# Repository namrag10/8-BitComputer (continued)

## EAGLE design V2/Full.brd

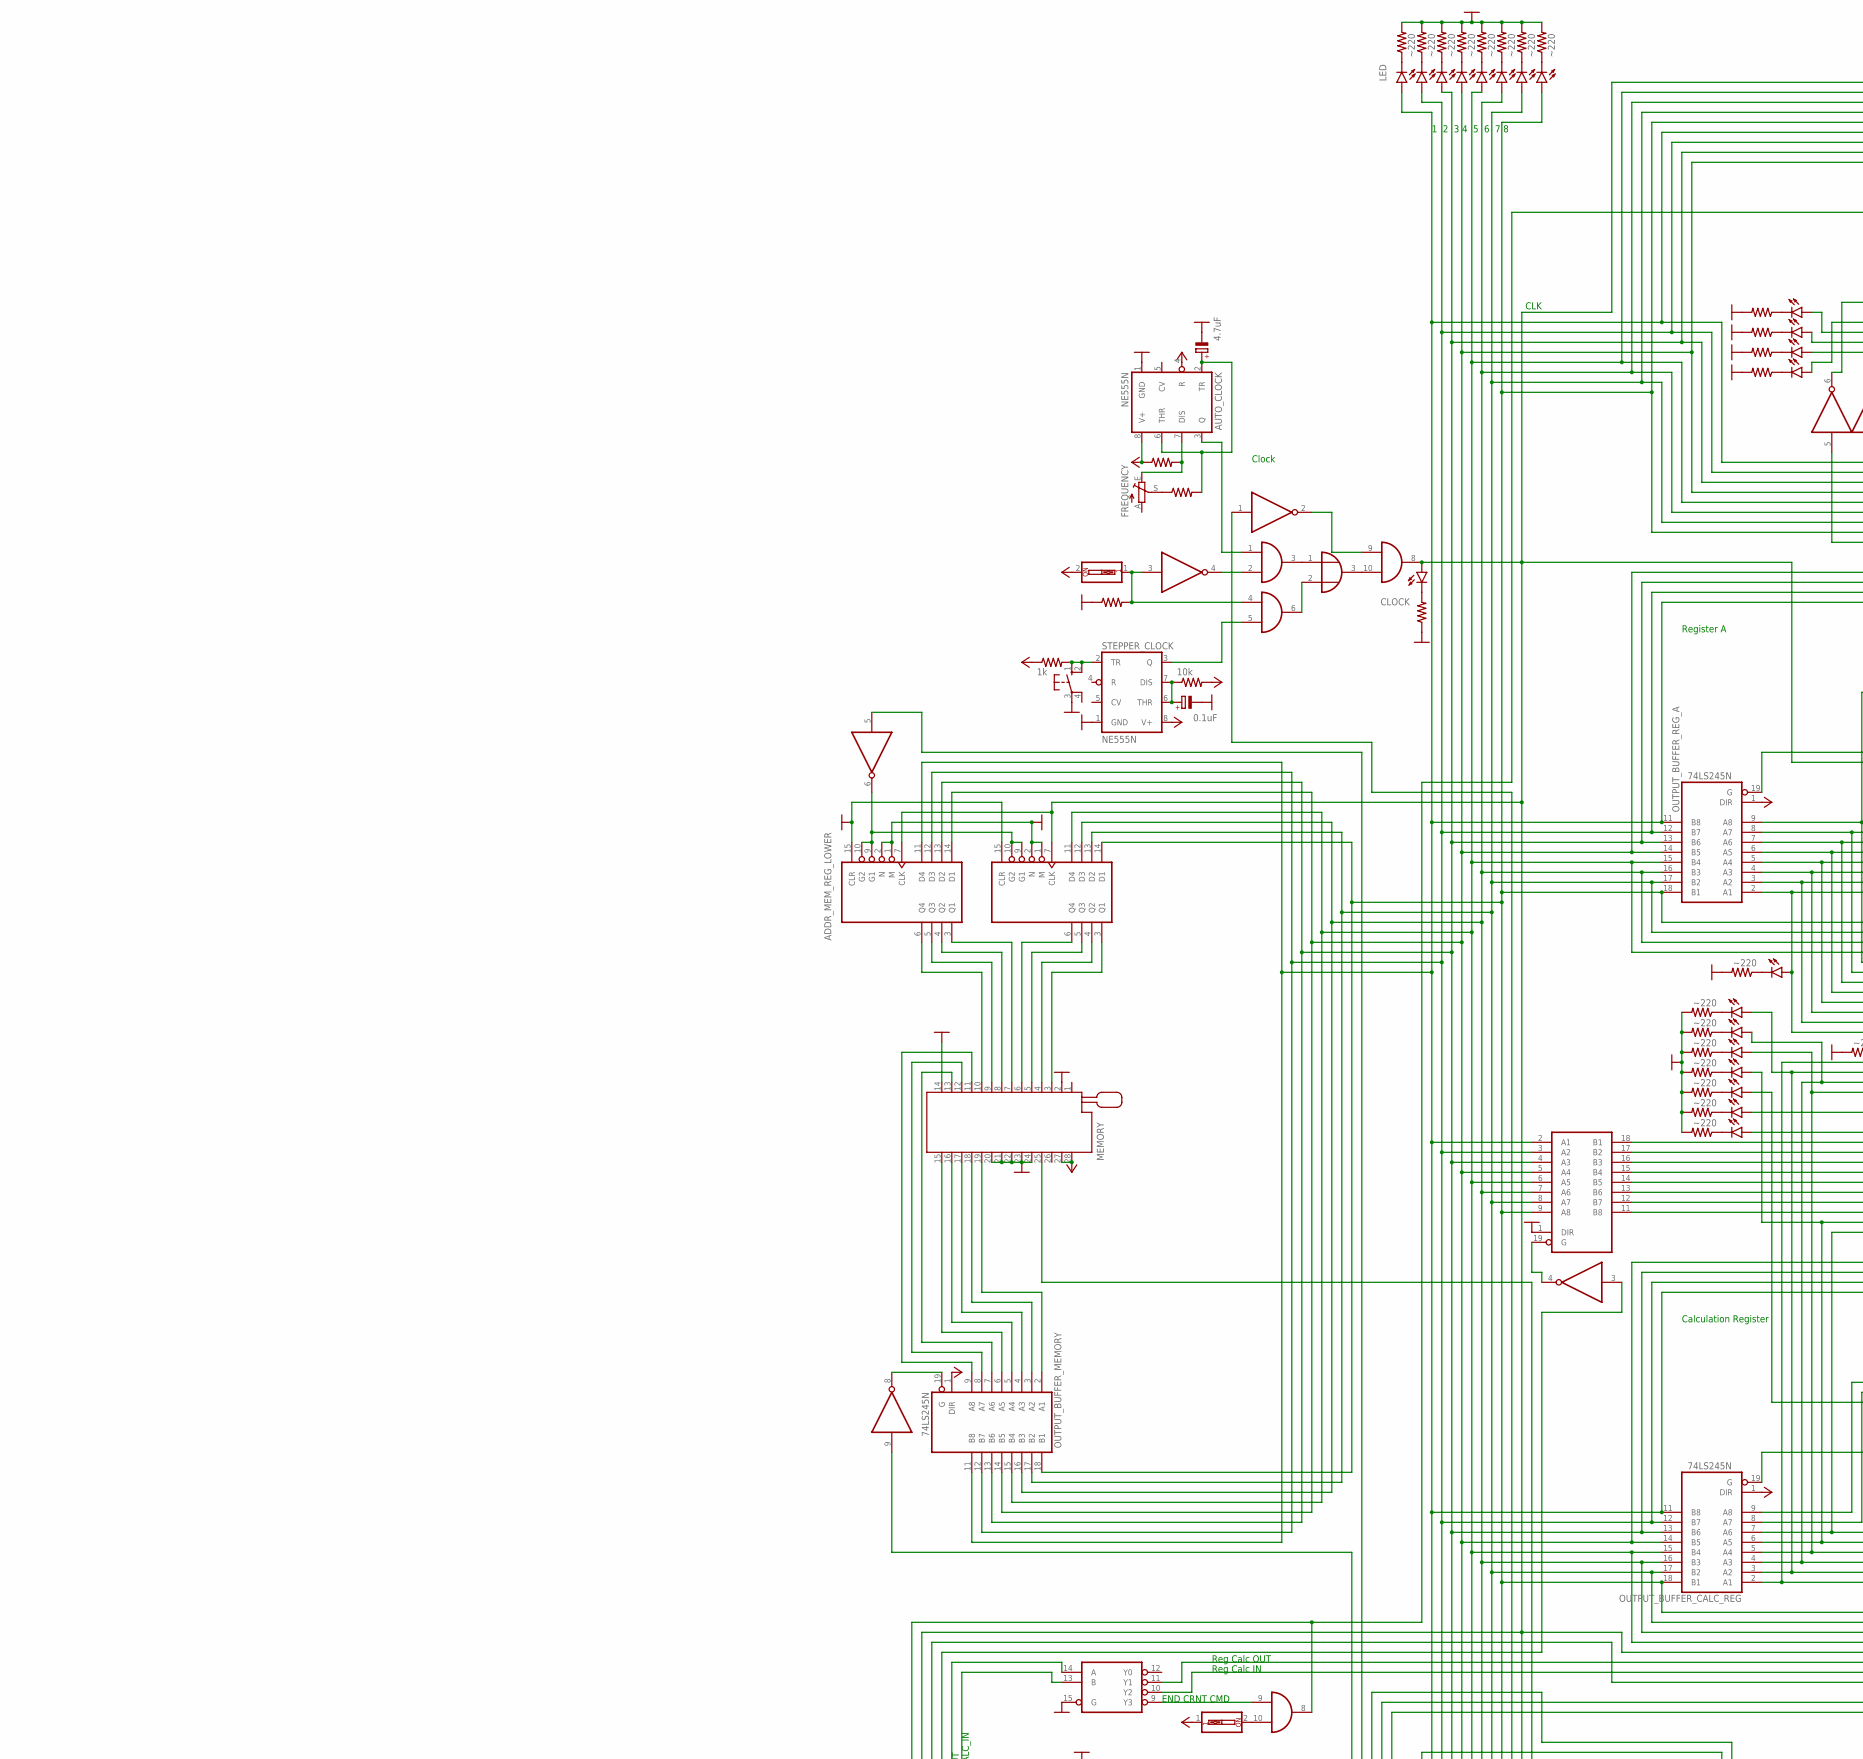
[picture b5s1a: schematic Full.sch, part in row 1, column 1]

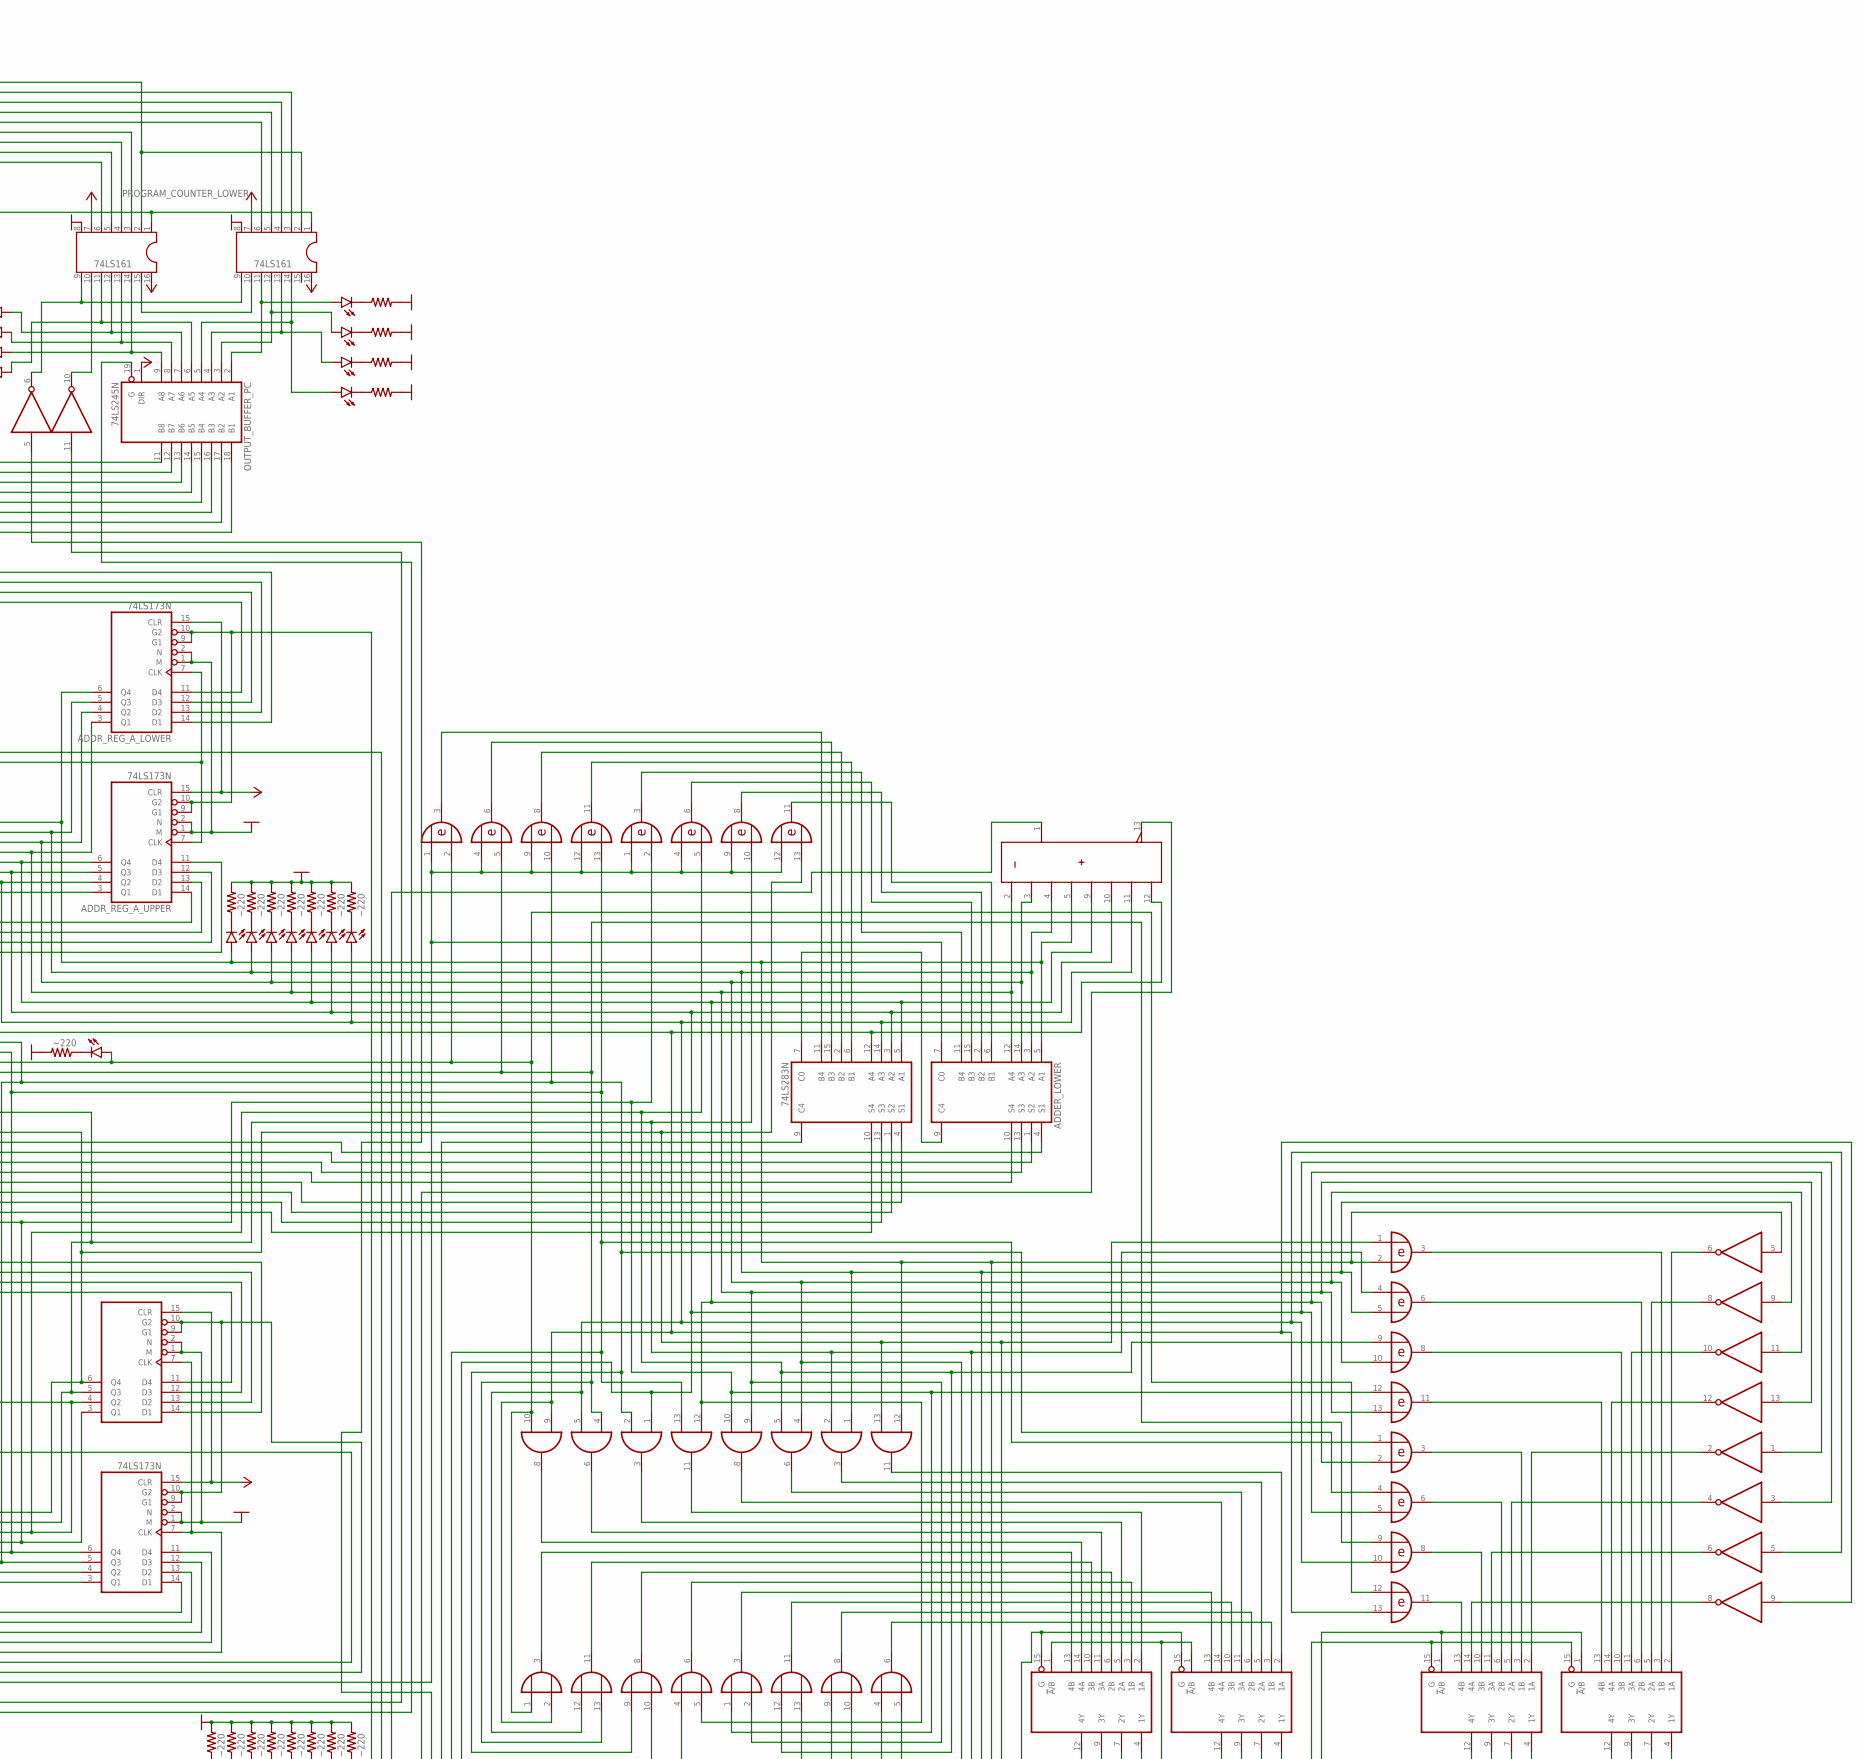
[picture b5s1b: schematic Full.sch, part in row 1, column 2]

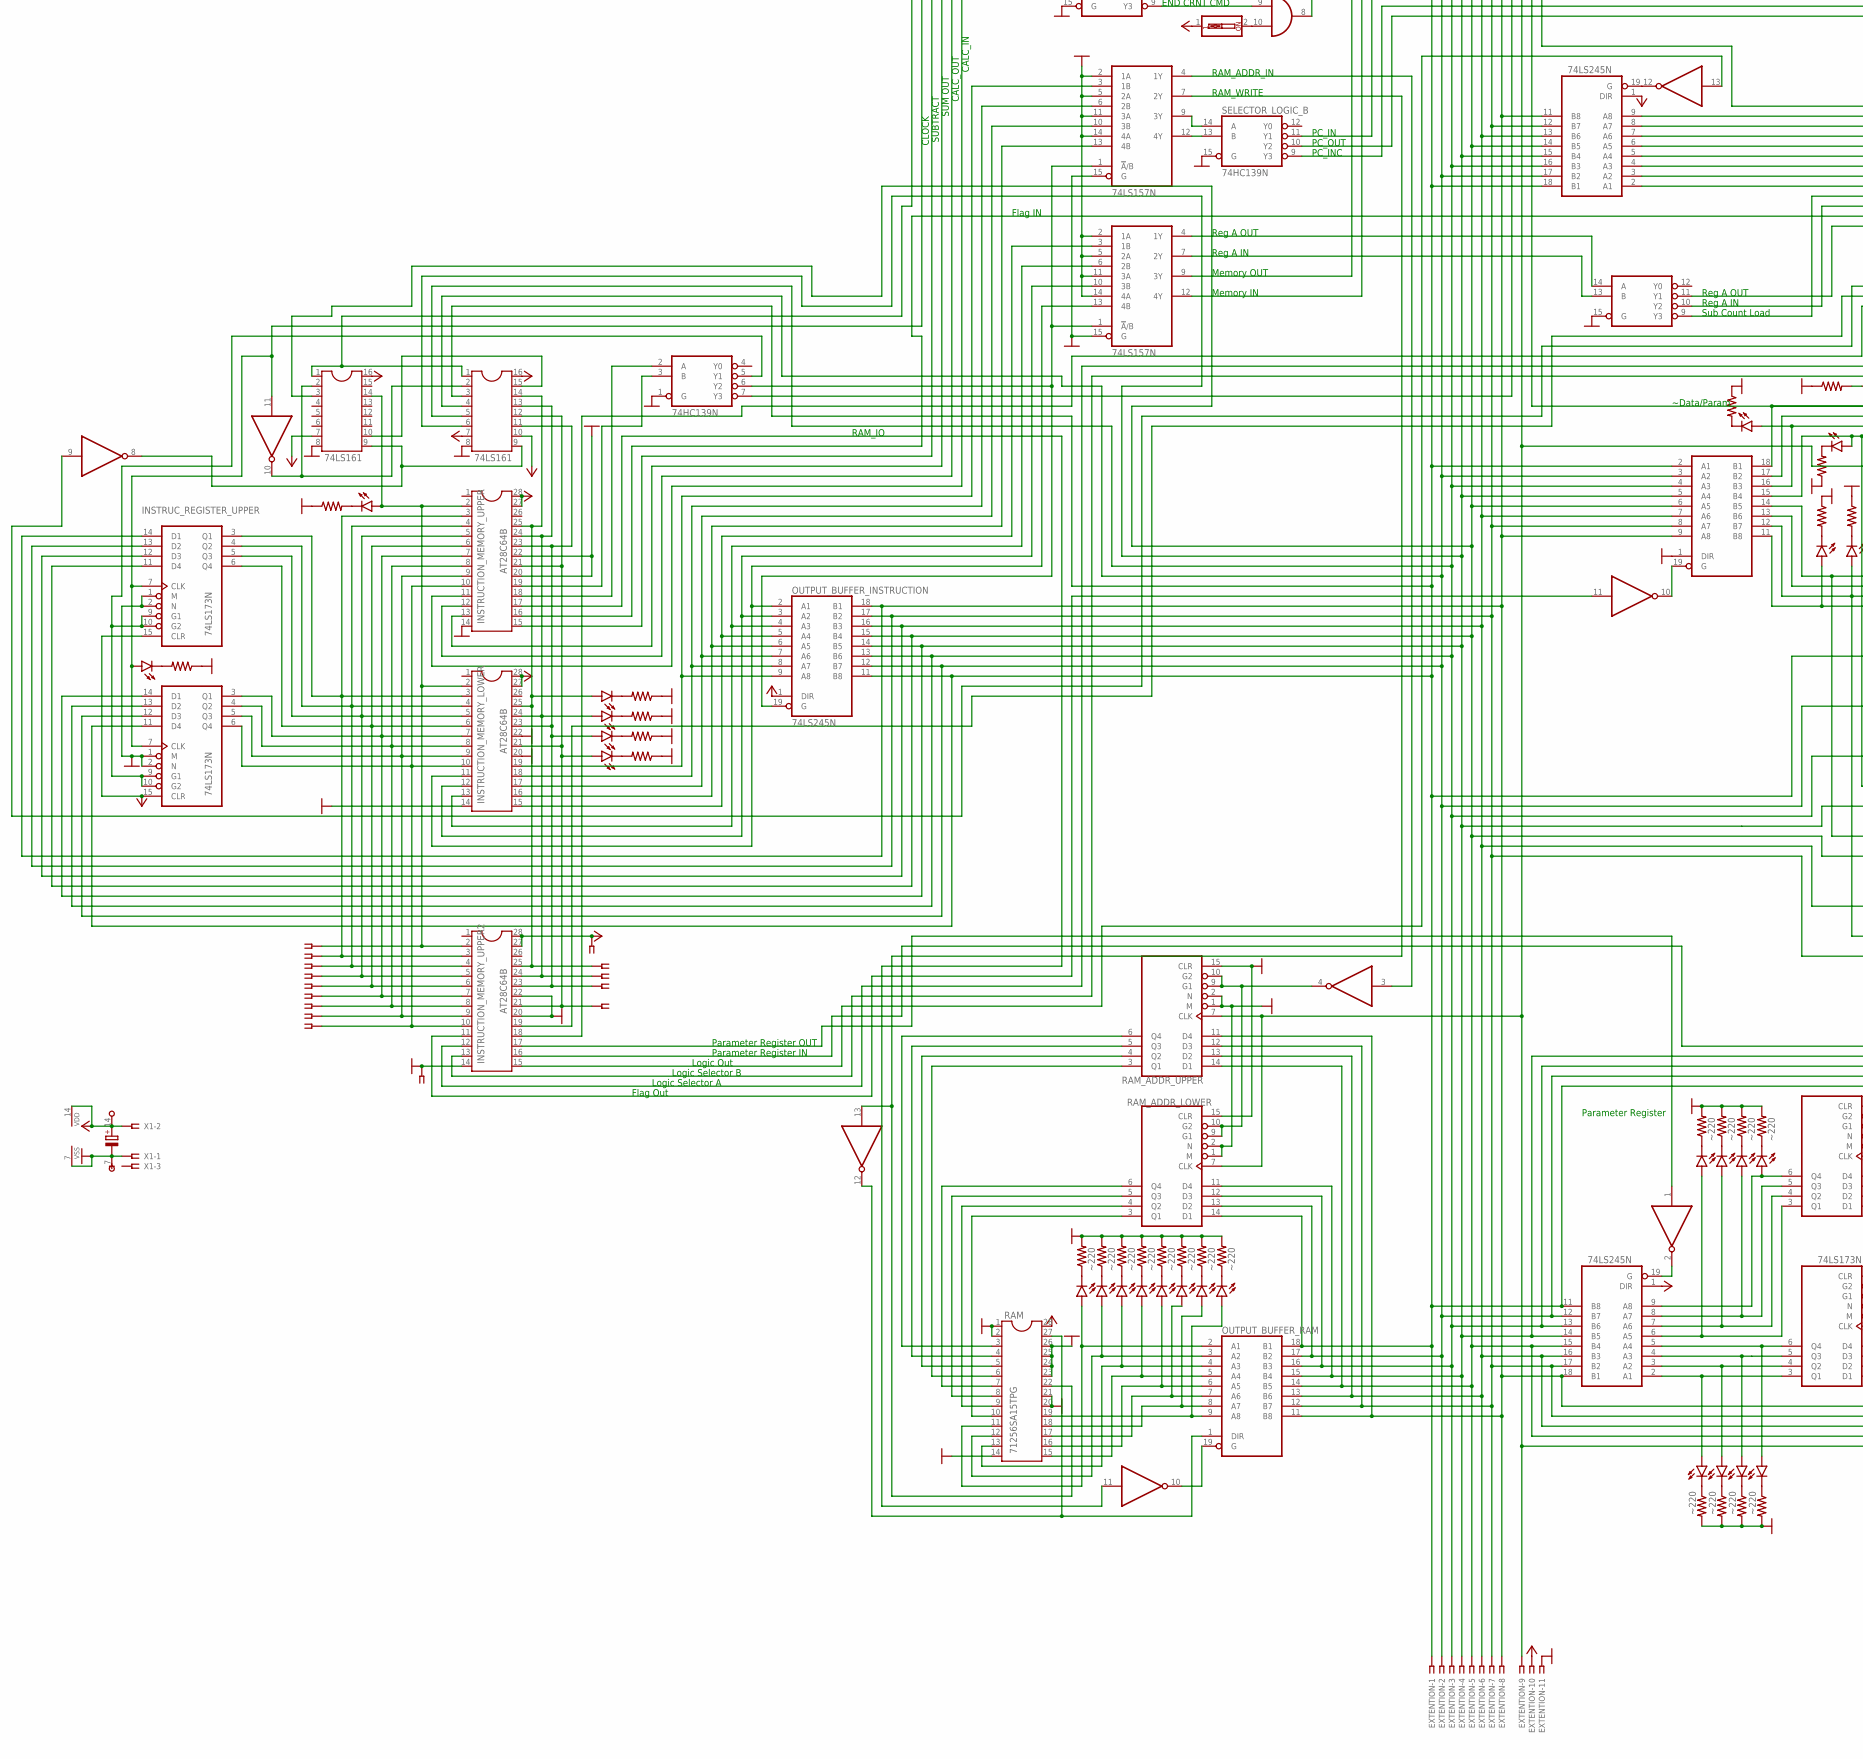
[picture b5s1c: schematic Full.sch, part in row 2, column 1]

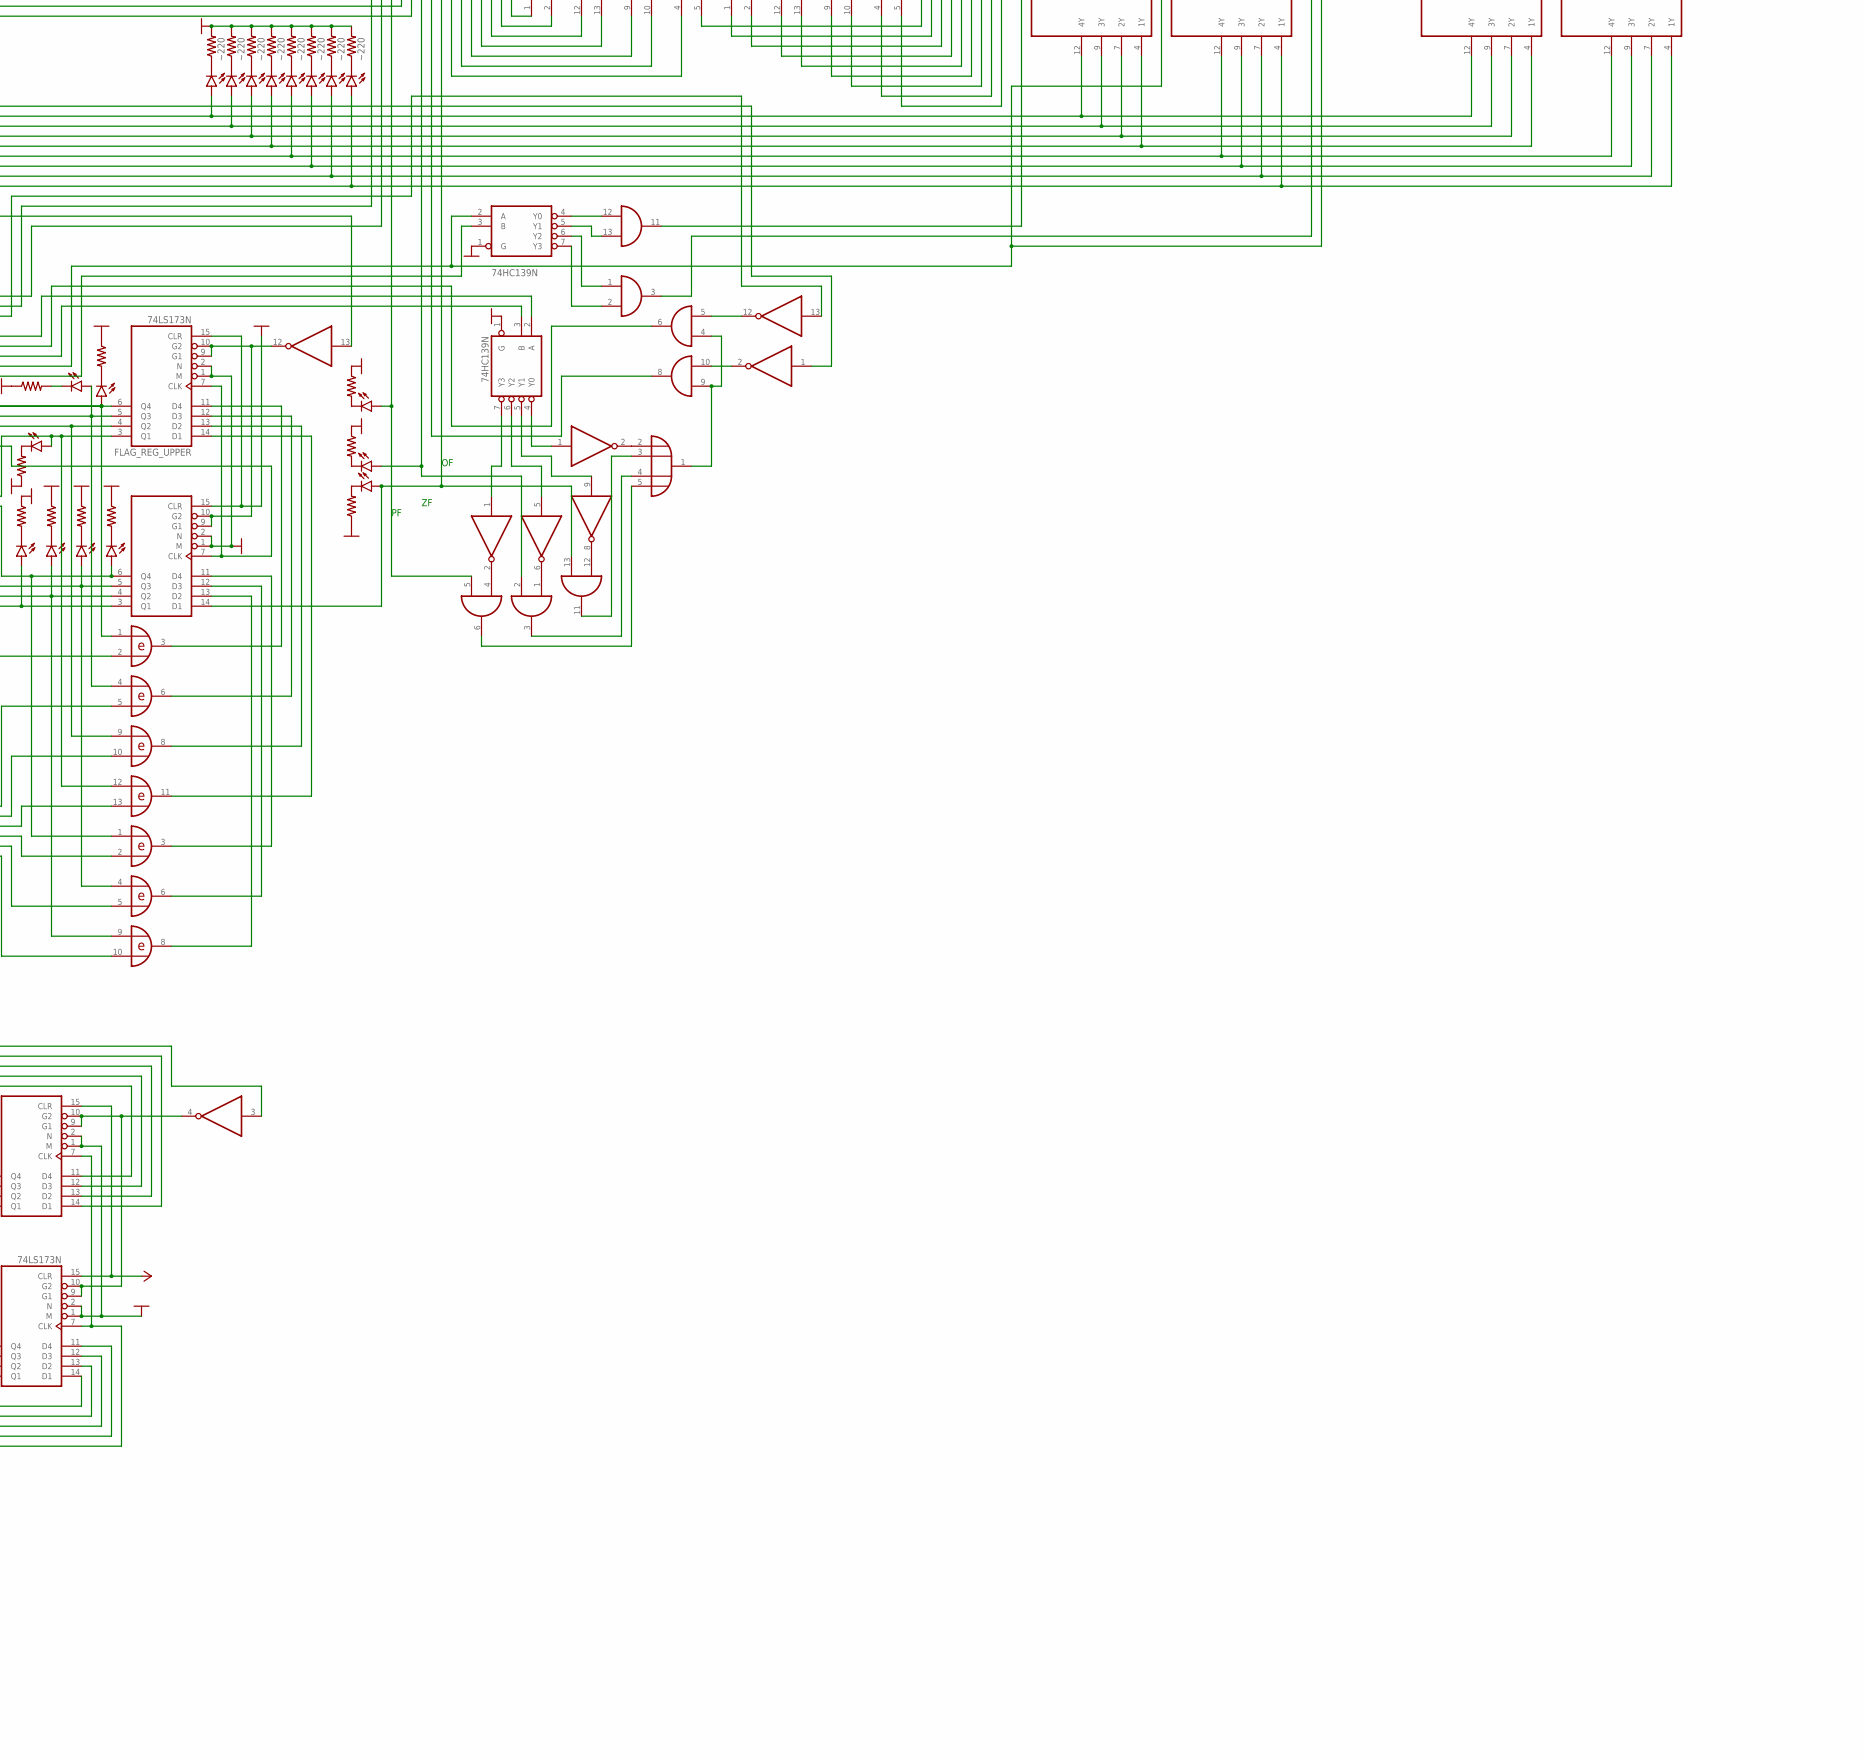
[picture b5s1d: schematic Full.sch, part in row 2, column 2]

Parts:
4_INP_OR_GATE: 4072N; DIL14
ADDER_LOWER: 74LS283N; DIL16
ADDER_UPPER: 74LS283N; DIL16
ADDR_MEM_REG_LOWER: 74LS173N; DIL16
ADDR_MEM_REG_UPPER: 74LS173N; DIL16
ADDR_REG_A_LOWER: 74LS173N; DIL16
ADDR_REG_A_UPPER: 74LS173N; DIL16
ADDR_REG_CALC_LOWER, ADDR_REG_CALC_LOWER1: 74LS173N; DIL16
ADDR_REG_CALC_UPPER: 74LS173N; DIL16
ADDR_REG_PARAM_UPPER: 74LS173N; DIL16
AND_GATE1_, AND_GATE2_, AND_GATE3_, AND_GATE4_: 74LS08N; DIL14
AND_GATE_: 74LS08N; DIL14
AUTO_CLOCK: NE555N; DIL08
BRANCH_SELECTOR: 74HC139N; DIL16
C1: 4.7uF; E2-5
C2, C3: 0.1uF; E2-5
CLK_MODE: SW_DIP-1; EDG-01
CLK_TRIGGER: 10-XX; B3F-10XX
CLOCK: LED5MM
DATABUS_1: LED; LED5MM
DATABUS_2, DATABUS_3, DATABUS_4, DATABUS_5, DATABUS_6, DATABUS_7, DATABUS_8: LED5MM
EXTENTION: SSW-111-02-G-S
FLAG_1, FLAG_2, FLAG_3, FLAG_4, FLAG_5, FLAG_6, FLAG_7, FLAG_8: LED5MM
FLAG_REG_LOWER: 74LS173N; DIL16
FLAG_REG_UPPER: 74LS173N; DIL16
FREQUENCY: 100k; RJ9W
INSRUCTION_REGISTER_SELECTOR_LOWER: 74LS157N; DIL16
INSRUCTION_REGISTER_SELECTOR_UPPER: 74LS157N; DIL16
INSTRUCTIONS_EXTENSION: SSW-115-02-G-S
INSTRUCTION_MEMORY_LOWER: AT28C64B; DIL28-6
INSTRUCTION_MEMORY_UPPER, INSTRUCTION_MEMORY_UPPER2: AT28C64B; DIL28-6
INSTRUC_REGISTER_LOWER: 74LS173N; DIL16
INSTRUC_REGISTER_UPPER: 74LS173N; DIL16
INVERTED_CLK_LED: LED5MM
KILL_SWITCH: SW_DIP-1; EDG-01
LED_A_REG_1, LED_A_REG_2, LED_A_REG_3, LED_A_REG_4, LED_A_REG_5, LED_A_REG_6, LED_A_REG_7, LED_A_REG_8: LED5MM
LED_B_REG_1, LED_B_REG_2, LED_B_REG_3, LED_B_REG_4, LED_B_REG_5, LED_B_REG_6, LED_B_REG_7, LED_B_REG_8: LED5MM
LOGIC_LED_1, LOGIC_LED_2, LOGIC_LED_3, LOGIC_LED_4, LOGIC_LED_5, LOGIC_LED_6, LOGIC_LED_7, LOGIC_LED_8: LED3MM
LOGIC_SELECTOR-AND/OR_LOWER: 74LS157N; DIL16
LOGIC_SELECTOR-AND/OR_UPPER: 74LS157N; DIL16
LOGIC_SELECTOR-XOR/NOT_LOWER: 74LS157N; DIL16
LOGIC_SELECTOR-XOR/NOT_UPPER: 74LS157N; DIL16
MEMORY: 228-1277-00-0602J
MICRO_COUNTER_LOWER: 74LS161; DIL16
MICRO_COUNTER_UPPER: 74LS161; DIL16
NOT_GATE1, NOT_GATE2_, NOT_GATE3_, NOT_GATE4_, NOT_GATE5_: 74LS04N; DIL14
NOT_GATE_: 74LS04N; DIL14
OR_GATE, OR_GATE1: 74LS32N; DIL14
OR_GATE_2: 74LS32N; DIL14
OUTPUT_BUFFER_ALU: 74LS245N; DIL20
OUTPUT_BUFFER_CALC_REG: 74LS245N; DIL20
OUTPUT_BUFFER_FLAGS: 74HC245N; DIL20
OUTPUT_BUFFER_INSTRUCTION: 74LS245N; DIL20
OUTPUT_BUFFER_LOGIC: 74LS245N; DIL20
OUTPUT_BUFFER_MEMORY: 74LS245N; DIL20
OUTPUT_BUFFER_PARAM_REG: 74LS245N; DIL20
OUTPUT_BUFFER_PC: 74LS245N; DIL20
OUTPUT_BUFFER_RAM: 74HC245N; DIL20
OUTPUT_BUFFER_REG_A: 74LS245N; DIL20
OVERFLOW_FLAG: LED5MM
PARAM_LED_1, PARAM_LED_2, PARAM_LED_3, PARAM_LED_4, PARAM_LED_5, PARAM_LED_6, PARAM_LED_7, PARAM_LED_8: LED3MM
PC_1, PC_2, PC_3, PC_4, PC_5, PC_6, PC_7, PC_8: LED5MM
POSITIVE_FLAG: LED5MM
PROGRAM_COUNTER_LOWER: 74LS161; DIL16
PROGRAM_COUNTER_UPPER: 74LS161; DIL16
R1, R2: 1k; 0204/7
R3: 10k; 0204/7
R4, R7: 220; 0204/7
R5, R6, R8, R9, R10, R11, R12, R13, R14, R15, R16, R17, R18, R19, R20, R21, R22, R23, R24, R25, R26, R27, R28, R29, R30, R31, R32, R33, R34, R35, R36, R37, R38, R39, R40, R41, R42, R43, R44, R45, R46, R47, R48, R49, R50, R51, R52, R53, R54, R55, R56, R57, R58, R59, R60, R61, R62, R63, R64, R65, R66, R67, R68, R69, R70, R71, R72, R73, R74, R75, R76, R77, R78, R79: ~220; 0204/7
RAM: 71256SA15TPG; DIL28-4
RAM_ADDR_LOWER: 74LS173N; DIL16
RAM_ADDR_UPPER: 74LS173N; DIL16
RAM_LED_1, RAM_LED_2, RAM_LED_3, RAM_LED_4, RAM_LED_5, RAM_LED_6, RAM_LED_7, RAM_LED_8: LED3MM
SELECTOR_LOGIC2_: 74HC139N; DIL16
SELECTOR_LOGIC_: 74HC139N; DIL16
STEPPER_CLOCK: NE555N; DIL08
SUBTRACT_INVRTR_LOWER_, SUBTRACT_INVRTR_LOWER_1: 74LS86N; DIL14
SUBTRACT_INVRTR_UPPER_, SUBTRACT_INVRTR_UPPER_1: 74LS86N; DIL14
USTEP_1, USTEP_2, USTEP_3, USTEP_4, USTEP_5: LED5MM
X1: SSW-103-02-G-S
XOR_GATE_1, XOR_GATE_2: 74LS86N; DIL14
ZERO_FLAG: LED5MM
ZERO_POS_FLAG_IDENTIFIER: 744078N; DIL14

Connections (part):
1_PLACE: ADDR_MEM_REG_LOWER.11 (D4), ADDR_REG_A_LOWER.11 (D4), ADDR_REG_CALC_LOWER.11 (D4), ADDR_REG_CALC_LOWER1.11 (D4), DATABUS_1.A, EXTENTION.1, INSTRUC_REGISTER_LOWER.11 (D4), MICRO_COUNTER_LOWER.3, OUTPUT_BUFFER_ALU.2 (A1), OUTPUT_BUFFER_CALC_REG.11 (B8), OUTPUT_BUFFER_FLAGS.2 (A1), OUTPUT_BUFFER_INSTRUCTION.11 (B8), OUTPUT_BUFFER_LOGIC.18 (B1), OUTPUT_BUFFER_MEMORY.11 (B8), OUTPUT_BUFFER_PARAM_REG.11 (B8), OUTPUT_BUFFER_PC.11 (B8), OUTPUT_BUFFER_RAM.18 (B1), OUTPUT_BUFFER_REG_A.11 (B8), PROGRAM_COUNTER_LOWER.3, RAM_ADDR_LOWER.14 (D1), XOR_GATE_1.2 (I1)
2_PLACE: ADDR_MEM_REG_LOWER.12 (D3), ADDR_REG_A_LOWER.12 (D3), ADDR_REG_CALC_LOWER.12 (D3), ADDR_REG_CALC_LOWER1.12 (D3), DATABUS_2.A, EXTENTION.2, INSTRUC_REGISTER_LOWER.12 (D3), MICRO_COUNTER_LOWER.4, OUTPUT_BUFFER_ALU.3 (A2), OUTPUT_BUFFER_CALC_REG.12 (B7), OUTPUT_BUFFER_FLAGS.3 (A2), OUTPUT_BUFFER_INSTRUCTION.12 (B7), OUTPUT_BUFFER_LOGIC.17 (B2), OUTPUT_BUFFER_MEMORY.12 (B7), OUTPUT_BUFFER_PARAM_REG.12 (B7), OUTPUT_BUFFER_PC.12 (B7), OUTPUT_BUFFER_RAM.17 (B2), OUTPUT_BUFFER_REG_A.12 (B7), PROGRAM_COUNTER_LOWER.4, RAM_ADDR_LOWER.13 (D2), XOR_GATE_1.5 (I1)
4_PLACE: ADDR_MEM_REG_LOWER.13 (D2), ADDR_REG_A_LOWER.13 (D2), ADDR_REG_CALC_LOWER.13 (D2), ADDR_REG_CALC_LOWER1.13 (D2), DATABUS_3.A, EXTENTION.3, INSTRUC_REGISTER_LOWER.13 (D2), MICRO_COUNTER_LOWER.5, OUTPUT_BUFFER_ALU.4 (A3), OUTPUT_BUFFER_CALC_REG.13 (B6), OUTPUT_BUFFER_FLAGS.4 (A3), OUTPUT_BUFFER_INSTRUCTION.13 (B6), OUTPUT_BUFFER_LOGIC.16 (B3), OUTPUT_BUFFER_MEMORY.13 (B6), OUTPUT_BUFFER_PARAM_REG.13 (B6), OUTPUT_BUFFER_PC.13 (B6), OUTPUT_BUFFER_RAM.16 (B3), OUTPUT_BUFFER_REG_A.13 (B6), PROGRAM_COUNTER_LOWER.5, RAM_ADDR_LOWER.12 (D3), XOR_GATE_1.10 (I1)
8_PLACE: ADDR_MEM_REG_LOWER.14 (D1), ADDR_REG_A_LOWER.14 (D1), ADDR_REG_CALC_LOWER.14 (D1), ADDR_REG_CALC_LOWER1.14 (D1), DATABUS_4.A, EXTENTION.4, INSTRUC_REGISTER_LOWER.14 (D1), MICRO_COUNTER_LOWER.6, OUTPUT_BUFFER_ALU.5 (A4), OUTPUT_BUFFER_CALC_REG.14 (B5), OUTPUT_BUFFER_FLAGS.5 (A4), OUTPUT_BUFFER_INSTRUCTION.14 (B5), OUTPUT_BUFFER_LOGIC.15 (B4), OUTPUT_BUFFER_MEMORY.14 (B5), OUTPUT_BUFFER_PARAM_REG.14 (B5), OUTPUT_BUFFER_PC.14 (B5), OUTPUT_BUFFER_RAM.15 (B4), OUTPUT_BUFFER_REG_A.14 (B5), PROGRAM_COUNTER_LOWER.6, RAM_ADDR_LOWER.11 (D4), XOR_GATE_1.13 (I1)
16_PLACE: ADDR_MEM_REG_UPPER.11 (D4), ADDR_REG_A_UPPER.11 (D4), ADDR_REG_CALC_UPPER.11 (D4), ADDR_REG_PARAM_UPPER.11 (D4), DATABUS_5.A, EXTENTION.5, INSTRUC_REGISTER_UPPER.11 (D4), MICRO_COUNTER_UPPER.3, OUTPUT_BUFFER_ALU.6 (A5), OUTPUT_BUFFER_CALC_REG.15 (B4), OUTPUT_BUFFER_FLAGS.6 (A5), OUTPUT_BUFFER_INSTRUCTION.15 (B4), OUTPUT_BUFFER_LOGIC.14 (B5), OUTPUT_BUFFER_MEMORY.15 (B4), OUTPUT_BUFFER_PARAM_REG.15 (B4), OUTPUT_BUFFER_PC.15 (B4), OUTPUT_BUFFER_RAM.14 (B5), OUTPUT_BUFFER_REG_A.15 (B4), PROGRAM_COUNTER_UPPER.3, RAM_ADDR_UPPER.14 (D1), XOR_GATE_2.2 (I1)
32_PLACE: ADDR_MEM_REG_UPPER.12 (D3), ADDR_REG_A_UPPER.12 (D3), ADDR_REG_CALC_UPPER.12 (D3), ADDR_REG_PARAM_UPPER.12 (D3), DATABUS_6.A, EXTENTION.6, INSTRUC_REGISTER_UPPER.12 (D3), OUTPUT_BUFFER_ALU.7 (A6), OUTPUT_BUFFER_CALC_REG.16 (B3), OUTPUT_BUFFER_FLAGS.7 (A6), OUTPUT_BUFFER_INSTRUCTION.16 (B3), OUTPUT_BUFFER_LOGIC.13 (B6), OUTPUT_BUFFER_MEMORY.16 (B3), OUTPUT_BUFFER_PARAM_REG.16 (B3), OUTPUT_BUFFER_PC.16 (B3), OUTPUT_BUFFER_RAM.13 (B6), OUTPUT_BUFFER_REG_A.16 (B3), PROGRAM_COUNTER_UPPER.4, RAM_ADDR_UPPER.13 (D2), XOR_GATE_2.5 (I1)
64_PLACE: ADDR_MEM_REG_UPPER.13 (D2), ADDR_REG_A_UPPER.13 (D2), ADDR_REG_CALC_UPPER.13 (D2), ADDR_REG_PARAM_UPPER.13 (D2), DATABUS_7.A, EXTENTION.7, INSTRUC_REGISTER_UPPER.13 (D2), OUTPUT_BUFFER_ALU.8 (A7), OUTPUT_BUFFER_CALC_REG.17 (B2), OUTPUT_BUFFER_FLAGS.8 (A7), OUTPUT_BUFFER_INSTRUCTION.17 (B2), OUTPUT_BUFFER_LOGIC.12 (B7), OUTPUT_BUFFER_MEMORY.17 (B2), OUTPUT_BUFFER_PARAM_REG.17 (B2), OUTPUT_BUFFER_PC.17 (B2), OUTPUT_BUFFER_RAM.12 (B7), OUTPUT_BUFFER_REG_A.17 (B2), PROGRAM_COUNTER_UPPER.5, RAM_ADDR_UPPER.12 (D3), XOR_GATE_2.10 (I1)
128_PLACE: ADDR_MEM_REG_UPPER.14 (D1), ADDR_REG_A_UPPER.14 (D1), ADDR_REG_CALC_UPPER.14 (D1), ADDR_REG_PARAM_UPPER.14 (D1), DATABUS_8.A, EXTENTION.8, INSTRUC_REGISTER_UPPER.14 (D1), OUTPUT_BUFFER_ALU.9 (A8), OUTPUT_BUFFER_CALC_REG.18 (B1), OUTPUT_BUFFER_FLAGS.9 (A8), OUTPUT_BUFFER_INSTRUCTION.18 (B1), OUTPUT_BUFFER_LOGIC.11 (B8), OUTPUT_BUFFER_MEMORY.18 (B1), OUTPUT_BUFFER_PARAM_REG.18 (B1), OUTPUT_BUFFER_PC.18 (B1), OUTPUT_BUFFER_RAM.11 (B8), OUTPUT_BUFFER_REG_A.18 (B1), PROGRAM_COUNTER_UPPER.6, RAM_ADDR_UPPER.11 (D4)
>0_FLAG: AND_GATE4_.5 (I1), POSITIVE_FLAG.A, ZERO_POS_FLAG_IDENTIFIER.1 (Y)
CALC_IN: ADDR_REG_CALC_LOWER.9 (G1), ADDR_REG_CALC_LOWER.10 (G2), ADDR_REG_CALC_UPPER.9 (G1), ADDR_REG_CALC_UPPER.10 (G2), SELECTOR_LOGIC2_.10 (Y2)
CALC_OUT: OUTPUT_BUFFER_CALC_REG.19 (G), SELECTOR_LOGIC2_.11 (Y1)
CLOCK: ADDR_MEM_REG_LOWER.7 (CLK), ADDR_MEM_REG_UPPER.7 (CLK), ADDR_REG_A_LOWER.7 (CLK), ADDR_REG_A_UPPER.7 (CLK), ADDR_REG_CALC_LOWER.7 (CLK), ADDR_REG_CALC_LOWER1.7 (CLK), ADDR_REG_CALC_UPPER.7 (CLK), ADDR_REG_PARAM_UPPER.7 (CLK), AND_GATE_.8 (O), CLOCK.A, EXTENTION.9, FLAG_REG_LOWER.7 (CLK), FLAG_REG_UPPER.7 (CLK), INSTRUC_REGISTER_LOWER.7 (CLK), INSTRUC_REGISTER_UPPER.7 (CLK), INVERTED_CLK_LED.A, NOT_GATE1.11 (I), PROGRAM_COUNTER_LOWER.2, PROGRAM_COUNTER_UPPER.2, RAM_ADDR_LOWER.7 (CLK), RAM_ADDR_UPPER.7 (CLK)
CTRL_SIG_5_(PC_OUT): INSRUCTION_REGISTER_SELECTOR_UPPER.13 (4B), INSTRUCTION_MEMORY_LOWER.16, OUTPUT_BUFFER_INSTRUCTION.6 (A5)
CTRL_SIG_6_(PC_IN): INSRUCTION_REGISTER_SELECTOR_UPPER.10 (3B), INSTRUCTION_MEMORY_LOWER.17, OUTPUT_BUFFER_INSTRUCTION.7 (A6)
CTRL_SIG_9_(CALC_REG_IN): INSTRUCTION_MEMORY_UPPER.11, SELECTOR_LOGIC2_.13 (B)
CTRL_SIG_10_(CALC_REG_OUT): INSTRUCTION_MEMORY_UPPER.12, SELECTOR_LOGIC2_.14 (A)
CTRL_SIG_11_(SUM_OUT): INSTRUCTION_MEMORY_UPPER.13, NOT_GATE3_.3 (I)
CTRL_SIG_12_(SUBTRACT): ADDER_LOWER.7 (C0), INSTRUCTION_MEMORY_UPPER.15, SUBTRACT_INVRTR_LOWER_.1 (I0), SUBTRACT_INVRTR_LOWER_.4 (I0), SUBTRACT_INVRTR_LOWER_.9 (I0), SUBTRACT_INVRTR_LOWER_.12 (I0), SUBTRACT_INVRTR_UPPER_.1 (I0), SUBTRACT_INVRTR_UPPER_.4 (I0), SUBTRACT_INVRTR_UPPER_.9 (I0), SUBTRACT_INVRTR_UPPER_.12 (I0)
END_CMD: AND_GATE4_.8 (O), MICRO_COUNTER_LOWER.1, MICRO_COUNTER_UPPER.1, PROGRAM_COUNTER_LOWER.1, PROGRAM_COUNTER_UPPER.1
FLAG_OUT: INSTRUCTION_MEMORY_UPPER2.11, NOT_GATE_.11 (I)
FLAG_TOGGLE_IN: INSTRUCTION_MEMORY_UPPER.16, NOT_GATE1.13 (I)
GND: 4_INP_OR_GATE.7 (VSS), ADDER_LOWER.8 (GND), ADDER_UPPER.8 (GND), ADDR_MEM_REG_LOWER.1 (M), ADDR_MEM_REG_LOWER.2 (N), ADDR_MEM_REG_LOWER.8 (GND), ADDR_MEM_REG_LOWER.15 (CLR), ADDR_MEM_REG_UPPER.1 (M), ADDR_MEM_REG_UPPER.2 (N), ADDR_MEM_REG_UPPER.8 (GND), ADDR_MEM_REG_UPPER.15 (CLR), ADDR_REG_A_LOWER.1 (M), ADDR_REG_A_LOWER.2 (N), ADDR_REG_A_LOWER.8 (GND), ADDR_REG_A_UPPER.1 (M), ADDR_REG_A_UPPER.2 (N), ADDR_REG_A_UPPER.8 (GND), ADDR_REG_CALC_LOWER.1 (M), ADDR_REG_CALC_LOWER.2 (N), ADDR_REG_CALC_LOWER.8 (GND), ADDR_REG_CALC_LOWER1.1 (M), ADDR_REG_CALC_LOWER1.2 (N), ADDR_REG_CALC_LOWER1.8 (GND), ADDR_REG_CALC_UPPER.1 (M), ADDR_REG_CALC_UPPER.2 (N), ADDR_REG_CALC_UPPER.8 (GND), ADDR_REG_PARAM_UPPER.1 (M), ADDR_REG_PARAM_UPPER.2 (N), ADDR_REG_PARAM_UPPER.8 (GND), AND_GATE1_.7 (GND), AND_GATE2_.7 (GND), AND_GATE3_.7 (GND), AND_GATE4_.7 (GND), AND_GATE_.7 (GND), AUTO_CLOCK.1 (GND), BRANCH_SELECTOR.1 (G), BRANCH_SELECTOR.8 (GND), BRANCH_SELECTOR.15 (G), C1.-, C2.-, C3.-, CLK_TRIGGER.3, EXTENTION.11, FLAG_REG_LOWER.1 (M), FLAG_REG_LOWER.2 (N), FLAG_REG_LOWER.8 (GND), FLAG_REG_LOWER.15 (CLR), FLAG_REG_UPPER.1 (M), FLAG_REG_UPPER.2 (N), FLAG_REG_UPPER.8 (GND), FLAG_REG_UPPER.15 (CLR), INSRUCTION_REGISTER_SELECTOR_LOWER.2 (1A), INSRUCTION_REGISTER_SELECTOR_LOWER.5 (2A), INSRUCTION_REGISTER_SELECTOR_LOWER.8 (GND), INSRUCTION_REGISTER_SELECTOR_LOWER.11 (3A), INSRUCTION_REGISTER_SELECTOR_LOWER.14 (4A), INSRUCTION_REGISTER_SELECTOR_LOWER.15 (G), INSRUCTION_REGISTER_SELECTOR_UPPER.2 (1A), INSRUCTION_REGISTER_SELECTOR_UPPER.5 (2A), INSRUCTION_REGISTER_SELECTOR_UPPER.8 (GND), INSRUCTION_REGISTER_SELECTOR_UPPER.11 (3A), INSRUCTION_REGISTER_SELECTOR_UPPER.14 (4A), INSRUCTION_REGISTER_SELECTOR_UPPER.15 (G), INSTRUCTIONS_EXTENSION.15, INSTRUCTION_MEMORY_LOWER.14, INSTRUCTION_MEMORY_LOWER.20, INSTRUCTION_MEMORY_LOWER.22, INSTRUCTION_MEMORY_UPPER.14, INSTRUCTION_MEMORY_UPPER.20, INSTRUCTION_MEMORY_UPPER.22, INSTRUCTION_MEMORY_UPPER2.14, INSTRUCTION_MEMORY_UPPER2.20, INSTRUCTION_MEMORY_UPPER2.22, INSTRUC_REGISTER_LOWER.1 (M), INSTRUC_REGISTER_LOWER.2 (N), INSTRUC_REGISTER_LOWER.8 (GND), INSTRUC_REGISTER_UPPER.1 (M), INSTRUC_REGISTER_UPPER.2 (N), INSTRUC_REGISTER_UPPER.8 (GND), LOGIC_SELECTOR-AND/OR_LOWER.8 (GND), LOGIC_SELECTOR-AND/OR_UPPER.8 (GND), LOGIC_SELECTOR-XOR/NOT_LOWER.8 (GND)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
HLT_SIGNAL: NOT_GATE1.1 (I), SELECTOR_LOGIC2_.7 (Y3)
INSTRUCTION_A0: INSTRUCTIONS_EXTENSION.1, INSTRUCTION_MEMORY_LOWER.10, INSTRUCTION_MEMORY_UPPER.10, INSTRUCTION_MEMORY_UPPER2.10, INSTRUC_REGISTER_LOWER.6 (Q4)
INSTRUCTION_A1: INSTRUCTIONS_EXTENSION.2, INSTRUCTION_MEMORY_LOWER.9, INSTRUCTION_MEMORY_UPPER.9, INSTRUCTION_MEMORY_UPPER2.9, INSTRUC_REGISTER_LOWER.5 (Q3)
INSTRUCTION_A2: INSTRUCTIONS_EXTENSION.3, INSTRUCTION_MEMORY_LOWER.8, INSTRUCTION_MEMORY_UPPER.8, INSTRUCTION_MEMORY_UPPER2.8, INSTRUC_REGISTER_LOWER.4 (Q2)
INSTRUCTION_A4: INSTRUCTIONS_EXTENSION.4, INSTRUCTION_MEMORY_LOWER.7, INSTRUCTION_MEMORY_UPPER.7, INSTRUCTION_MEMORY_UPPER2.7, INSTRUC_REGISTER_LOWER.3 (Q1)
INSTRUCTION_A5: INSTRUCTIONS_EXTENSION.6, INSTRUCTION_MEMORY_LOWER.5, INSTRUCTION_MEMORY_UPPER.5, INSTRUCTION_MEMORY_UPPER2.5, INSTRUC_REGISTER_UPPER.5 (Q3)
INSTRUCTION_A6: INSTRUCTIONS_EXTENSION.7, INSTRUCTION_MEMORY_LOWER.4, INSTRUCTION_MEMORY_UPPER.4, INSTRUCTION_MEMORY_UPPER2.4, INSTRUC_REGISTER_UPPER.4 (Q2)
INSTRUCTION_A7: INSTRUCTIONS_EXTENSION.8, INSTRUCTION_MEMORY_LOWER.3, INSTRUCTION_MEMORY_UPPER.3, INSTRUCTION_MEMORY_UPPER2.3, INSTRUC_REGISTER_UPPER.3 (Q1)
INSTRUCTION_IN: INSTRUC_REGISTER_LOWER.9 (G1), INSTRUC_REGISTER_LOWER.10 (G2), INSTRUC_REGISTER_UPPER.9 (G1), INSTRUC_REGISTER_UPPER.10 (G2), SELECTOR_LOGIC2_.5 (Y1)
INSTRUCTION_OUTPUT: INSRUCTION_REGISTER_SELECTOR_LOWER.1 (!A!/B), INSRUCTION_REGISTER_SELECTOR_UPPER.1 (!A!/B), OUTPUT_BUFFER_INSTRUCTION.19 (G), SELECTOR_LOGIC2_.6 (Y2)
INSTRUCTION__A4: INSTRUCTIONS_EXTENSION.5, INSTRUCTION_MEMORY_LOWER.6, INSTRUCTION_MEMORY_UPPER.6, INSTRUCTION_MEMORY_UPPER2.6, INSTRUC_REGISTER_UPPER.6 (Q4)
INVERTED_CLOCK: MICRO_COUNTER_LOWER.2, MICRO_COUNTER_UPPER.2, NOT_GATE1.10 (O)
INV_HLT_SIGNAL: AND_GATE_.9 (I0), NOT_GATE1.2 (O)
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
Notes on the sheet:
Register A
Clock
1 2 3 4 5 6 7 8
Flag IN
Calculation Register
CLK
~Data/Param
CALC_IN
CALC_OUT
SUM OUT
SUBTRACT
Reg A OUT
Reg A IN
Memory OUT
Memory IN
RAM_WRITE
RAM_ADDR_IN
RAM_IO
Parameter Register
PC_OUT
PC_IN
PC_INC
CLOCK
Flag Out
Logic Selector A
Logic Selector B
Logic Out
Parameter Register IN
Parameter Register OUT
Sub Count Load
Reg Calc OUT
Reg Calc IN
END CRNT CMD

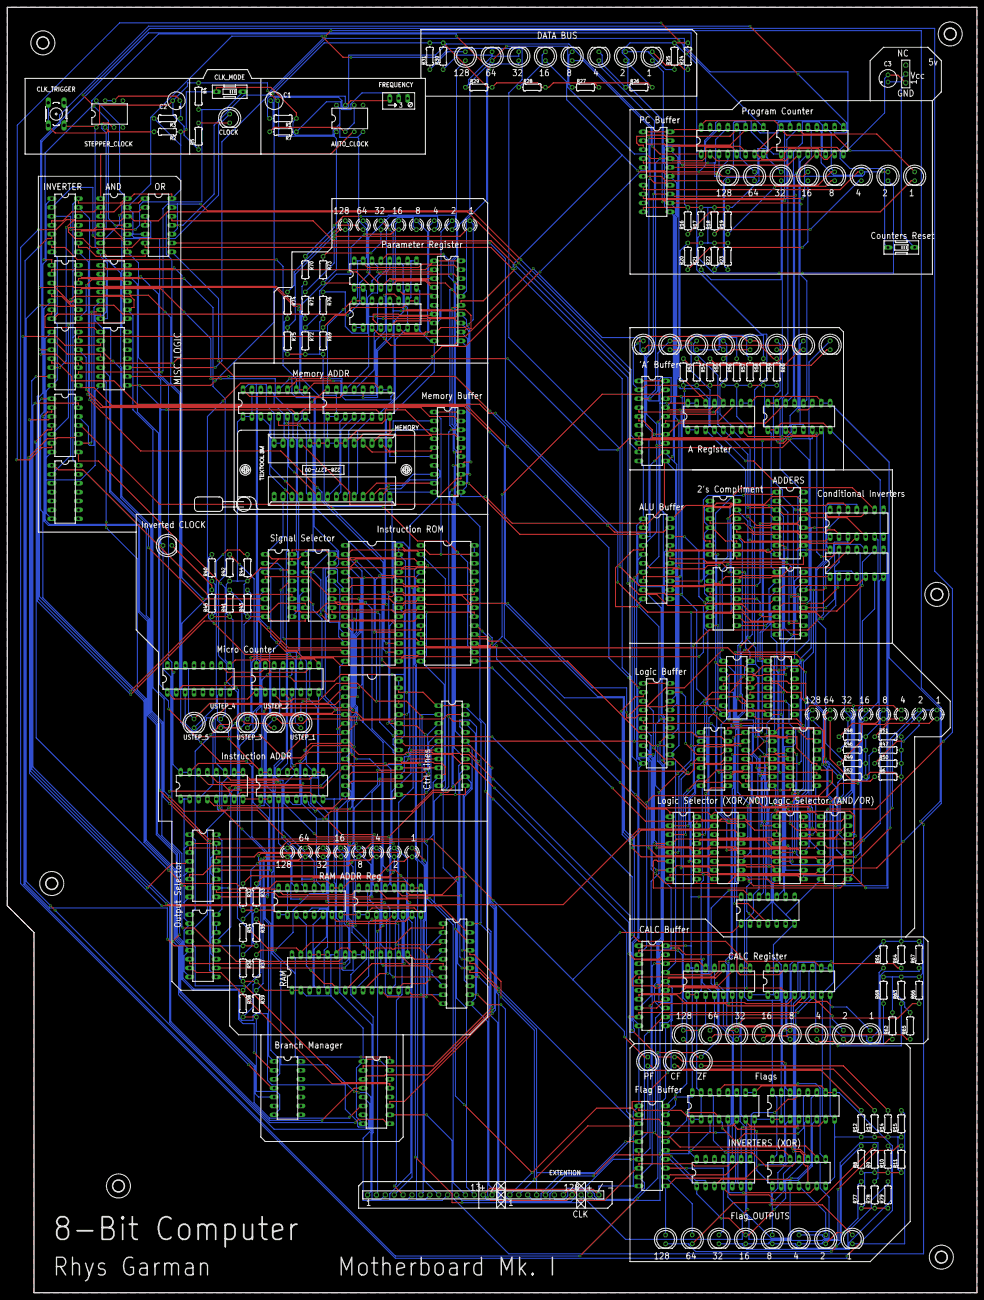
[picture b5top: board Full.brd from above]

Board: 2 copper layers, 276.9 x 367.0 mm, 237 parts (0 on the bottom side), 335 nets.

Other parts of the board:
U$1, U$2, U$3, U$4, U$5, U$6: 3,3
